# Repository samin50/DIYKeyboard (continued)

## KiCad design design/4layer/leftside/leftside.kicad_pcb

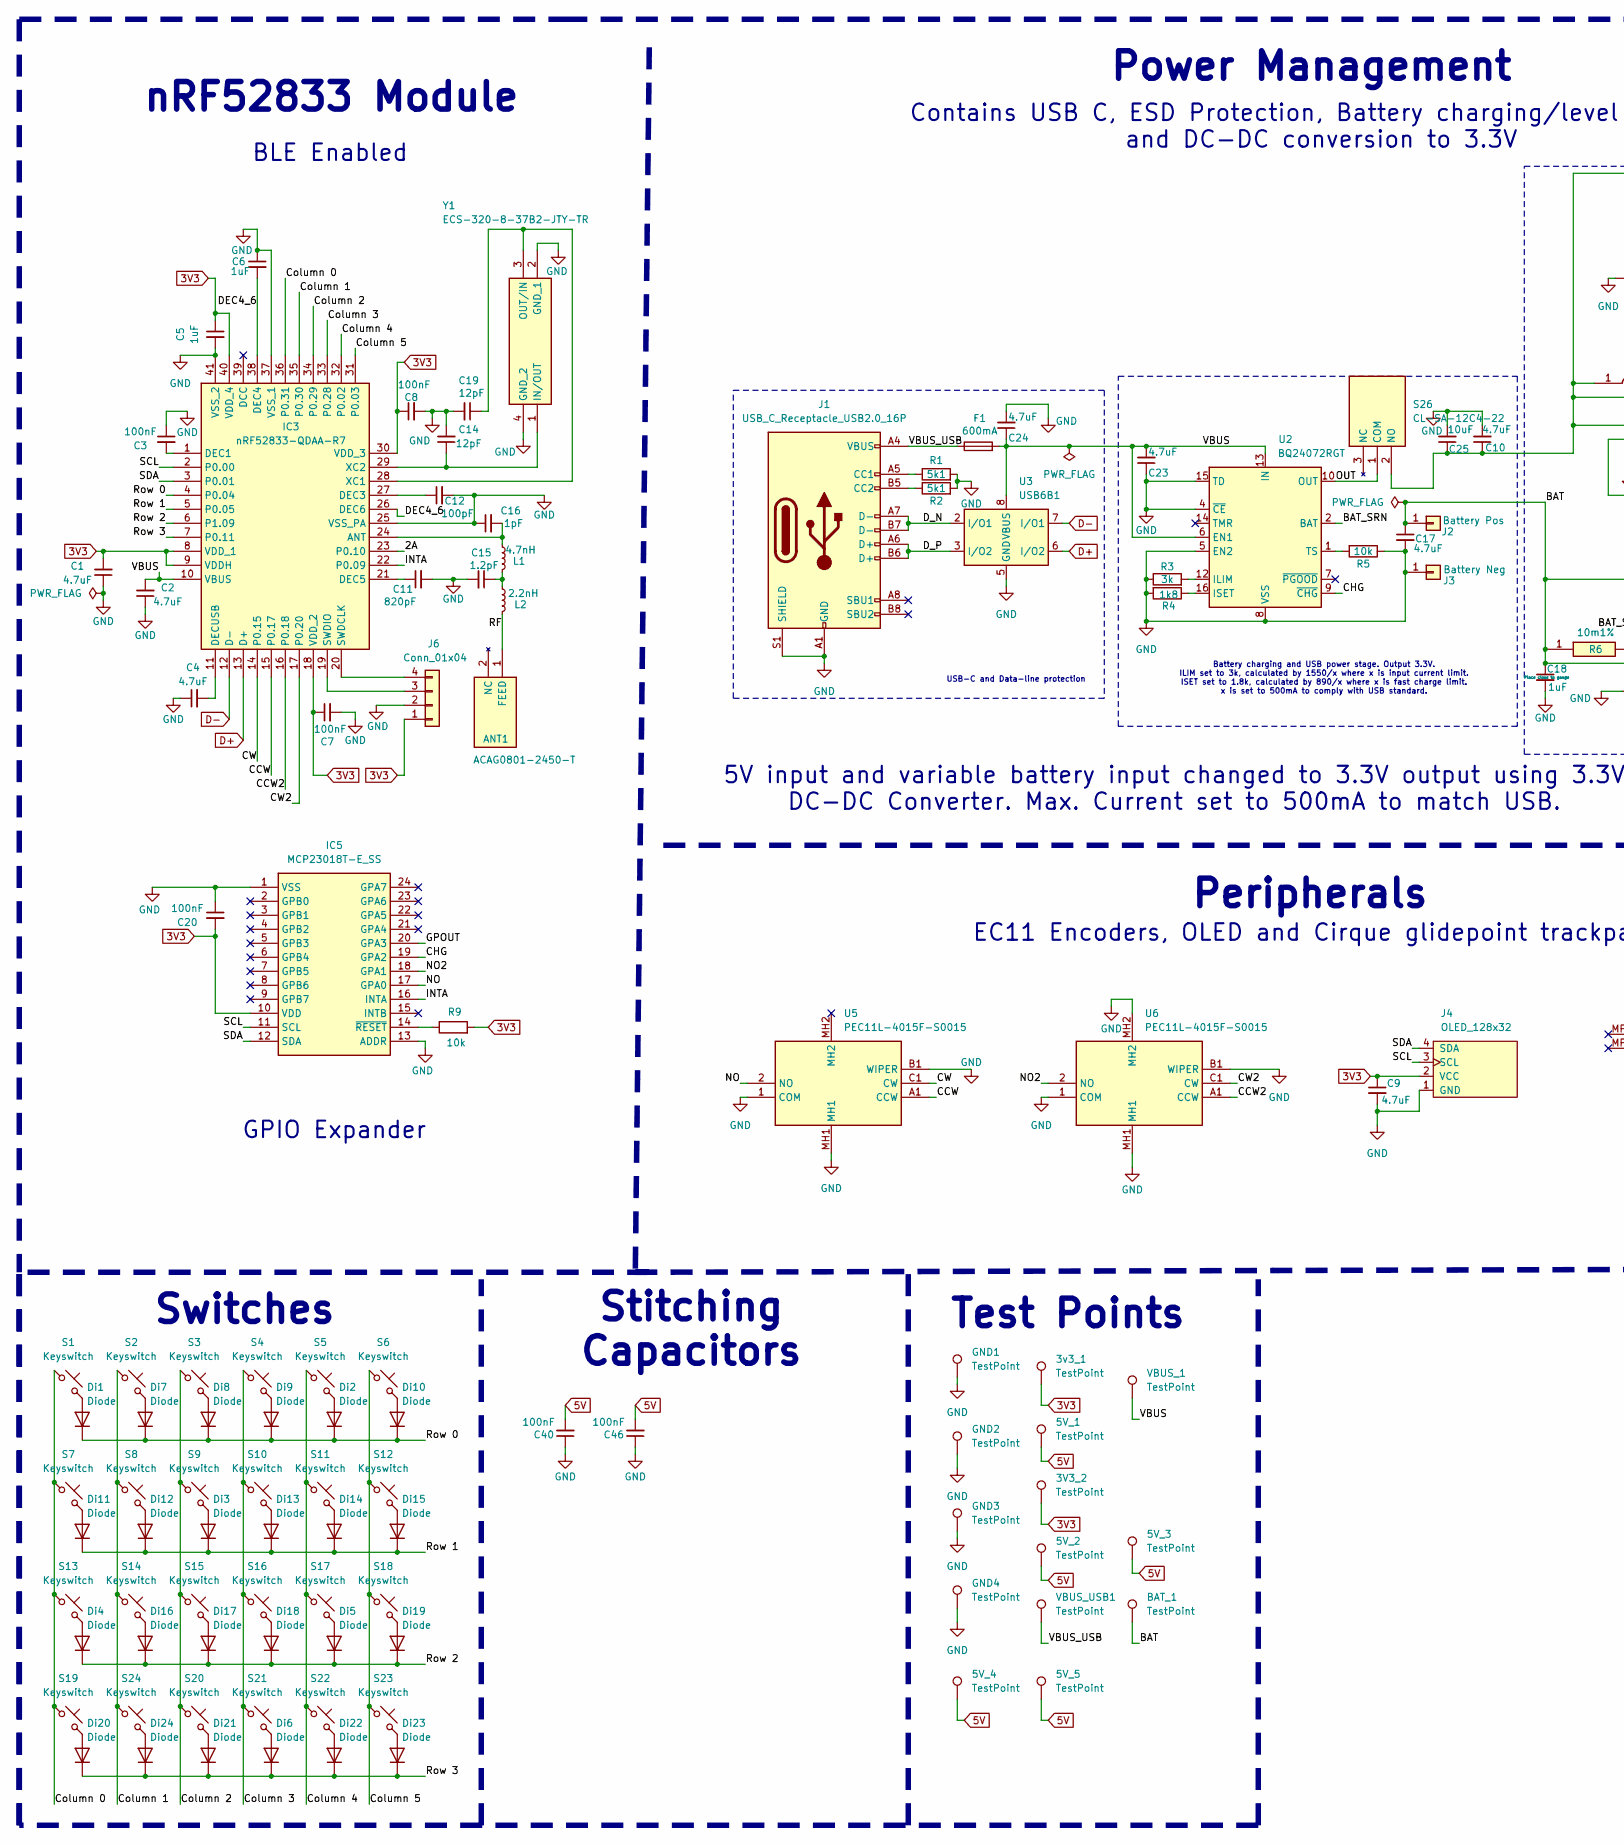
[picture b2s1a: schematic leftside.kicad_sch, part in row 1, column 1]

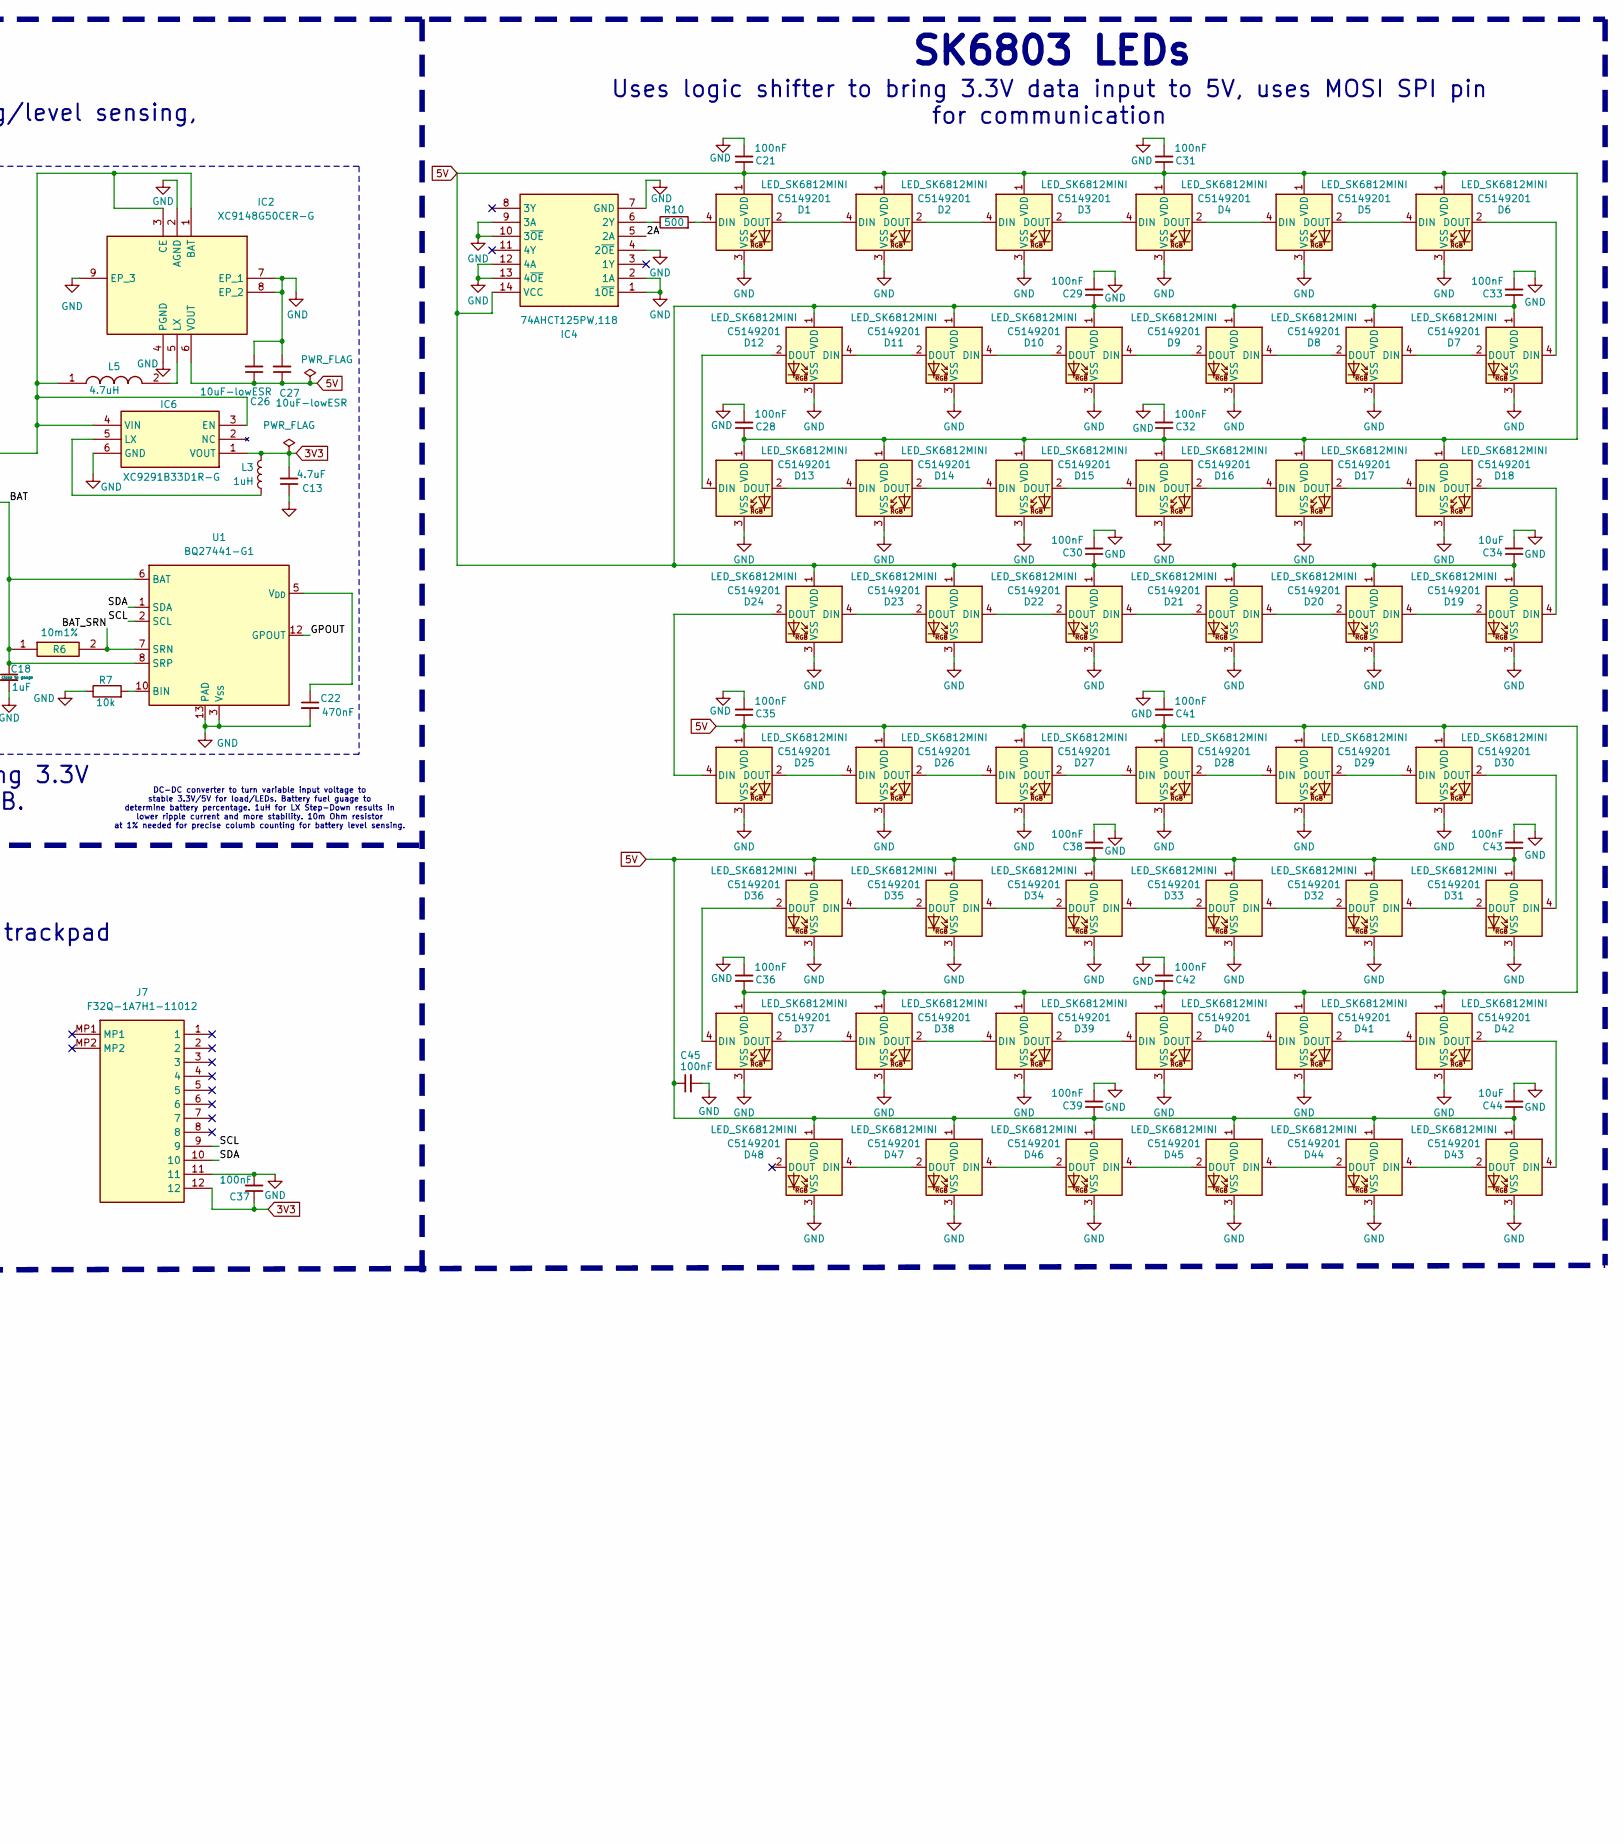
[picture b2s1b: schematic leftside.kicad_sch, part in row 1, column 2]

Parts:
3V3_2, 3v3_1, 5V_1, 5V_2, 5V_3, 5V_4, 5V_5: TestPoint; TestPoint_Pad_D1.5mm
ANT1: ACAG0801-2450-T; ANTC8010X110N; Mouser Part Number 815-G0801-2450-T
BAT_1: TestPoint; TestPoint_Pad_D1.5mm
C1, C2, C4, C9, C10, C13, C17, C23, C24: 4.7uF; Capacitor_0603
C3, C7, C8, C20, C21, C28, C29, C30, C31, C32, C33, C35, C36, C37, C38, C39, C40, C41, C42, C43, C45, C46: 100nF; Capacitor_0603
C5, C6, C18: 1uF; Capacitor_0603
C11: 820pF; Capacitor_0603
C12: 100pF; Capacitor_0603
C14, C19: 12pF; Capacitor_0603
C15: 1.2pF; Capacitor_0603
C16: 1pF; Capacitor_0603
C22: 470nF; Capacitor_0603
C25, C34, C44: 10uF; Capacitor_0603
C26, C27: 10uF-lowESR; Capacitor_0603
D1, D2, D3, D4, D5, D6, D7, D8, D9, D10, D11, D12, D13, D14, D15, D16, D17, D18, D19, D20, D21, D22, D23, D24, D25, D26, D27, D28, D29, D30, D31, D32, D33, D34, D35, D36, D37, D38, D39, D40, D41, D42, D43, D44, D45, D46, D47, D48: LED_SK6812MINI; LCSC C5149201
Di1, Di2, Di3, Di4, Di5, Di6, Di7, Di8, Di9, Di10, Di11, Di12, Di13, Di14, Di15, Di16, Di17, Di18, Di19, Di20, Di21, Di22, Di23, Di24: Diode; Diode_SOD-123
F1: 600mA; 0603L050SLYR
GND1, GND2, GND3, GND4: TestPoint; TestPoint_Pad_D1.5mm
IC2: XC9148G50CER-G; XC9147_8_USP-6C; Mouser Part Number 865-XC9148G50CER-G
IC3: nRF52833-QDAA-R7; QFN40P500X500X90-41N-D; Mouser Part Number 949-NRF52833-QDAA-R7
IC4: 74AHCT125PW,118; SOP65P640X110-14N; Mouser Part Number 771-AHCT125PW118
IC5: MCP23018T-E_SS; SOP65P780X200-24N; Mouser Part Number 579-MCP23018T-E/SS
IC6: XC9291B33D1R-G; XC9290A07E1RG; Manufacturer_Part_Number XC9291B33D1R-G
J1: USB_C_Receptacle_USB2.0_16P; USB_C_Receptacle_HRO_TYPE-C-31-M-12
J2: Battery Pos; SolderWire-2.5sqmm_1x01_D2.4mm_OD3.6mm
J3: Battery Neg; SolderWire-2.5sqmm_1x01_D2.4mm_OD3.6mm
J4: OLED_128x32
J6: Conn_01x04; PinHeader_1x04_P2.54mm_Vertical
J7: F32Q-1A7H1-11012; F32Q1A7H111012; Mouser Part Number 649-F32Q-1A7H1-11012
L1: 4.7nH; L_0603_1608Metric
L2: 2.2nH; L_0603_1608Metric
L3: 1uH; L_0603_1608Metric
L5: 4.7uH; INDC1608X80N; Mouser Part Number 963-MCHK1608T1R0MKN
R1, R2: 5k1; R_0603_1608Metric
R3: 3k; R_0603_1608Metric
R4: 1k8; R_0603_1608Metric
R5, R7, R9: 10k; R_0603_1608Metric
R6: 10m1%; RESC2012X41N; Mouser Part Number 660-TLR2ATTD10L0F
R10: 500; R_0603_1608Metric
S1, S2, S3, S4, S5, S6, S7, S8, S9, S10, S11, S12, S13, S14, S15, S16, S17, S18, S19, S20, S21, S22, S23, S24: Keyswitch; Hotswap_Choc_V1V2_Plated_1.00u
S26: CL-SA-12C4-22; CLSA12C422; Mouser Part Number 229-CL-SA-12C4-22
U1: BQ27441-G1; Texas_S-PDSO-N12
U2: BQ24072RGT; VQFN-16-1EP_3x3mm_P0.5mm_EP1.6x1.6mm
U3: USB6B1; SOIC-8_3.9x4.9mm_P1.27mm
U5, U6: PEC11L-4015F-S0015; PEC11L4015FS0015; Mouser Part Number 652-PEC11L4015FS0015
VBUS_1: TestPoint; TestPoint_Pad_D1.5mm
VBUS_USB1: TestPoint; TestPoint_Pad_D1.5mm
Y1: ECS-320-8-37B2-JTY-TR; ECS320837B2JTYTR; Mouser Part Number 520-320-8-37B2-JTYTR

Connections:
3V3: 3V3_2.1, 3v3_1.1, C1.2, C5.1, C7.1, C8.1, C9.1, C13.2, C20.2, C37.1, IC3.8 (VDD_1), IC3.9 (VDDH), IC3.18 (VDD_2), IC3.30 (VDD_3), IC3.40 (VDD_4), IC5.10 (VDD), IC6.1 (VOUT), J4.2 (VCC), J6.1, J7.12, L3.1, R9.2
5V: 5V_1.1, 5V_2.1, 5V_3.1, 5V_4.1, 5V_5.1, C21.1, C26.1, C27.1, C28.1, C29.1, C30.1, C31.1, C32.1, C33.1, C34.1, C35.1, C36.1, C38.1, C39.1, C40.2, C41.1, C42.1, C43.1, C44.1, C45.1, C46.2, D1.1 (VDD), D2.1 (VDD), D3.1 (VDD), D4.1 (VDD), D5.1 (VDD), D6.1 (VDD), D7.1 (VDD), D8.1 (VDD), D9.1 (VDD), D10.1 (VDD), D11.1 (VDD), D12.1 (VDD), D13.1 (VDD), D14.1 (VDD), D15.1 (VDD), D16.1 (VDD), D17.1 (VDD), D18.1 (VDD), D19.1 (VDD), D20.1 (VDD), D21.1 (VDD), D22.1 (VDD), D23.1 (VDD), D24.1 (VDD), D25.1 (VDD), D26.1 (VDD), D27.1 (VDD), D28.1 (VDD), D29.1 (VDD), D30.1 (VDD), D31.1 (VDD), D32.1 (VDD), D33.1 (VDD), D34.1 (VDD), D35.1 (VDD), D36.1 (VDD), D37.1 (VDD), D38.1 (VDD), D39.1 (VDD), D40.1 (VDD), D41.1 (VDD), D42.1 (VDD), D43.1 (VDD), D44.1 (VDD), D45.1 (VDD), D46.1 (VDD), D47.1 (VDD), D48.1 (VDD), IC2.6 (VOUT), IC4.14 (VCC)
/2A: IC3.23 (P0.10), IC4.5 (2A)
/BAT: BAT_1.1, C17.1, C18.1, J2.1, R6.1, U1.6 (BAT), U1.8 (SRP)
/BAT_SRN: R6.2, U1.7 (SRN), U2.2 (BAT), U2.3 (BAT)
/CCW: IC3.15 (P0.17), U5.A1 (CCW)
/CCW2: IC3.16 (P0.18), U6.A1 (CCW)
/CHG: IC5.19 (GPA2), U2.9 (~CHG)
/CW: IC3.14 (P0.15), U5.C1 (CW)
/CW2: IC3.17 (P0.20), U6.C1 (CW)
/Column 0: IC3.36 (P0.31), S1.1, S7.1, S13.1, S19.1
/Column 1: IC3.35 (P0.30), S2.1, S8.1, S14.1, S24.1
/Column 2: IC3.34 (P0.29), S3.1, S9.1, S15.1, S20.1
/Column 3: IC3.33 (P0.28), S4.1, S10.1, S16.1, S21.1
/Column 4: IC3.32 (P0.02), S5.1, S11.1, S17.1, S22.1
/Column 5: IC3.31 (P0.03), S6.1, S12.1, S18.1, S23.1
/DEC4_6: C6.2, IC3.26 (DEC6), IC3.38 (DEC4)
/D_N: J1.A7 (D-), J1.B7 (D-), U3.2 (I/O1)
/D_P: J1.A6 (D+), J1.B6 (D+), U3.3 (I/O2)
/GPOUT: IC5.20 (GPA3), U1.12 (GPOUT)
/INTA: IC3.22 (P0.09), IC5.16 (INTA)
/NO: IC5.17 (GPA0), U5.2 (NO)
/NO2: IC5.18 (GPA1), U6.2 (NO)
/OUT: S26.1 (COM), U2.10 (OUT), U2.11 (OUT)
/RF: ANT1.1 (FEED), L2.1
/Row 0: Di1.1 (K), Di2.1 (K), Di7.1 (K), Di8.1 (K), Di9.1 (K), Di10.1 (K), IC3.4 (P0.04)
/Row 1: Di3.1 (K), Di11.1 (K), Di12.1 (K), Di13.1 (K), Di14.1 (K), Di15.1 (K), IC3.5 (P0.05)
/Row 2: Di4.1 (K), Di5.1 (K), Di16.1 (K), Di17.1 (K), Di18.1 (K), Di19.1 (K), IC3.6 (P1.09)
/Row 3: Di6.1 (K), Di20.1 (K), Di21.1 (K), Di22.1 (K), Di23.1 (K), Di24.1 (K), IC3.7 (P0.11)
/SCL: IC3.2 (P0.00), IC5.11 (SCL), J4.3 (SCL), J7.9, U1.2 (SCL)
/SDA: IC3.3 (P0.01), IC5.12 (SDA), J4.4 (SDA), J7.10, U1.1 (SDA)
/VBUS: C2.2, C23.2, C24.1, F1.2, IC3.10 (VBUS), U2.6 (EN1), U2.13 (IN), U3.1 (VBUS), U3.8 (VBUS), VBUS_1.1
/VBUS_USB: F1.1, J1.A4 (VBUS), J1.A9 (VBUS), J1.B4 (VBUS), J1.B9 (VBUS), VBUS_USB1.1
D+: IC3.13 (D+), U3.6 (I/O2)
D-: IC3.12 (D-), U3.7 (I/O1)
GND: C1.1, C2.1, C3.1, C4.1, C5.2, C6.1, C7.2, C8.2, C9.2, C10.2, C11.2, C12.2, C13.1, C14.2, C15.2, C16.1, C17.2, C18.2, C19.2, C20.1, C21.2, C22.2, C23.1, C24.2, C25.2, C26.2, C27.2, C28.2, C29.2, C30.2, C31.2, C32.2, C33.2, C34.2, C35.2, C36.2, C37.2, C38.2, C39.2, C40.1, C41.2, C42.2, C43.2, C44.2, C45.2, C46.1, D1.3 (VSS), D2.3 (VSS), D3.3 (VSS), D4.3 (VSS), D5.3 (VSS), D6.3 (VSS), D7.3 (VSS), D8.3 (VSS), D9.3 (VSS), D10.3 (VSS), D11.3 (VSS), D12.3 (VSS), D13.3 (VSS), D14.3 (VSS), D15.3 (VSS), D16.3 (VSS), D17.3 (VSS), D18.3 (VSS), D19.3 (VSS), D20.3 (VSS), D21.3 (VSS), D22.3 (VSS), D23.3 (VSS), D24.3 (VSS), D25.3 (VSS), D26.3 (VSS), D27.3 (VSS), D28.3 (VSS), D29.3 (VSS), D30.3 (VSS), D31.3 (VSS), D32.3 (VSS), D33.3 (VSS), D34.3 (VSS), D35.3 (VSS), D36.3 (VSS), D37.3 (VSS), D38.3 (VSS), D39.3 (VSS), D40.3 (VSS), D41.3 (VSS), D42.3 (VSS), D43.3 (VSS), D44.3 (VSS), D45.3 (VSS), D46.3 (VSS), D47.3 (VSS), D48.3 (VSS), GND1.1, GND2.1, GND3.1, GND4.1, IC2.2 (AGND), IC2.4 (PGND), IC2.7 (EP_1), IC2.8 (EP_2), IC2.9 (EP_3), IC3.25 (VSS_PA), IC3.37 (VSS_1), IC3.41 (VSS_2), IC4.1 (1~OE), IC4.2 (1A), IC4.4 (2~OE), IC4.7 (GND), IC4.9 (3A), IC4.10 (3~OE), IC4.12 (4A), IC4.13 (4~OE), IC5.1 (VSS), IC5.13 (ADDR), IC6.6 (GND), J1.A1 (GND), J1.A12 (GND), J1.B1 (GND), J1.B12 (GND), J1.S1 (SHIELD), J3.1, J4.1 (GND), J6.2, J7.11, R1.2, R2.2, R3.1, R4.2, R5.1, R7.1, U1.3 (V_{SS}), U1.13 (PAD), U2.4 (~CE), U2.5 (EN2), U2.8 (VSS), U2.15 (TD), U2.17 (VSS), U3.4 (GND), U3.5 (GND), U5.1 (COM), U5.B1 (WIPER), U5.MH1, U6.1 (COM), U6.B1 (WIPER), U6.MH1, U6.MH2, Y1.2 (GND_1), Y1.4 (GND_2)
unnamed: C15.1, L1.2, L2.2
unnamed: D1.4 (DIN), R10.2
unnamed: D1.2 (DOUT), D2.4 (DIN)
unnamed: D2.2 (DOUT), D3.4 (DIN)
unnamed: D3.2 (DOUT), D4.4 (DIN)
unnamed: D4.2 (DOUT), D5.4 (DIN)
unnamed: D5.2 (DOUT), D6.4 (DIN)
unnamed: D6.2 (DOUT), D7.4 (DIN)
unnamed: D7.2 (DOUT), D8.4 (DIN)
unnamed: D8.2 (DOUT), D9.4 (DIN)
unnamed: D9.2 (DOUT), D10.4 (DIN)
unnamed: D10.2 (DOUT), D11.4 (DIN)
unnamed: D11.2 (DOUT), D12.4 (DIN)
unnamed: D12.2 (DOUT), D13.4 (DIN)
unnamed: D13.2 (DOUT), D14.4 (DIN)
unnamed: D14.2 (DOUT), D15.4 (DIN)
unnamed: D15.2 (DOUT), D16.4 (DIN)
unnamed: D16.2 (DOUT), D17.4 (DIN)
unnamed: D17.2 (DOUT), D18.4 (DIN)
unnamed: D18.2 (DOUT), D19.4 (DIN)
unnamed: D19.2 (DOUT), D20.4 (DIN)
unnamed: D20.2 (DOUT), D21.4 (DIN)
unnamed: D21.2 (DOUT), D22.4 (DIN)
unnamed: D22.2 (DOUT), D23.4 (DIN)
unnamed: D23.2 (DOUT), D24.4 (DIN)
unnamed: D24.2 (DOUT), D25.4 (DIN)
unnamed: D25.2 (DOUT), D26.4 (DIN)
unnamed: D26.2 (DOUT), D27.4 (DIN)
unnamed: D27.2 (DOUT), D28.4 (DIN)
unnamed: D28.2 (DOUT), D29.4 (DIN)
unnamed: D29.2 (DOUT), D30.4 (DIN)
unnamed: D30.2 (DOUT), D31.4 (DIN)
unnamed: D31.2 (DOUT), D32.4 (DIN)
unnamed: D32.2 (DOUT), D33.4 (DIN)
unnamed: D33.2 (DOUT), D34.4 (DIN)
unnamed: D34.2 (DOUT), D35.4 (DIN)
unnamed: D35.2 (DOUT), D36.4 (DIN)
unnamed: D36.2 (DOUT), D37.4 (DIN)
unnamed: D37.2 (DOUT), D38.4 (DIN)
unnamed: D38.2 (DOUT), D39.4 (DIN)
unnamed: D39.2 (DOUT), D40.4 (DIN)
unnamed: D40.2 (DOUT), D41.4 (DIN)
unnamed: D41.2 (DOUT), D42.4 (DIN)
unnamed: D42.2 (DOUT), D43.4 (DIN)
unnamed: D43.2 (DOUT), D44.4 (DIN)
unnamed: D44.2 (DOUT), D45.4 (DIN)
unnamed: D45.2 (DOUT), D46.4 (DIN)
unnamed: D46.2 (DOUT), D47.4 (DIN)
unnamed: D47.2 (DOUT), D48.4 (DIN)
unnamed: Di1.2 (A), S1.2
unnamed: Di2.2 (A), S5.2
unnamed: Di3.2 (A), S9.2
unnamed: Di4.2 (A), S13.2
unnamed: Di5.2 (A), S17.2
unnamed: Di6.2 (A), S21.2
unnamed: Di7.2 (A), S2.2
unnamed: Di8.2 (A), S3.2
unnamed: Di9.2 (A), S4.2
unnamed: Di10.2 (A), S6.2
unnamed: Di11.2 (A), S7.2
unnamed: Di12.2 (A), S8.2
unnamed: Di13.2 (A), S10.2
unnamed: Di14.2 (A), S11.2
unnamed: Di15.2 (A), S12.2
unnamed: Di16.2 (A), S14.2
unnamed: Di17.2 (A), S15.2
unnamed: Di18.2 (A), S16.2
unnamed: Di19.2 (A), S18.2
unnamed: Di20.2 (A), S19.2
unnamed: Di21.2 (A), S20.2
unnamed: Di22.2 (A), S22.2
unnamed: Di23.2 (A), S23.2
unnamed: Di24.2 (A), S24.2
unnamed: C10.1, C25.1, IC2.1 (BAT), IC2.3 (CE), IC6.3 (EN), IC6.4 (VIN), L5.1, S26.2 (NO)
unnamed: IC2.5 (LX), L5.2
unnamed: C16.2, IC3.24 (ANT), L1.1
unnamed: C3.2, IC3.1 (DEC1)
unnamed: C12.1, IC3.27 (DEC3)
unnamed: C11.1, IC3.21 (DEC5)
unnamed: C4.2, IC3.11 (DECUSB)
unnamed: IC3.20 (SWDCLK), J6.4
unnamed: IC3.19 (SWDIO), J6.3
unnamed: C19.1, IC3.28 (XC1), Y1.3 (OUT/IN)
unnamed: C14.1, IC3.29 (XC2), Y1.1 (IN/OUT)
unnamed: IC4.6 (2Y), R10.1
unnamed: IC5.14 (~RESET), R9.1
unnamed: IC6.5 (LX), L3.2
unnamed: J1.A5 (CC1), R1.1
unnamed: J1.B5 (CC2), R2.1
unnamed: R7.2, U1.10 (BIN)
unnamed: C22.1, U1.5 (V_{DD})
unnamed: R3.2, U2.12 (ILIM)
unnamed: R4.1, U2.16 (ISET)
unnamed: R5.2, U2.1 (TS)

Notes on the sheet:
Test Points
SK6803 LEDs
nRF52833 Module
GPIO Expander
BLE Enabled
DC-DC converter to turn variable input voltage to stable 3.3V/5V for load/LEDs. Battery fuel guage to determine battery percentage. 1uH for LX Step-Down results in lower ripple current and more stability. 10m Ohm resistor at 1% needed for precise columb counting for battery level sensing.
Power Management
Battery charging and USB power stage. Output 3.3V. ILIM set to 3k, calculated by 1550/x where x is input current limit. ISET set to 1.8k, calculated by 890/x where x is fast charge limit. x is set to 500mA to comply with USB standard.
USB-C and Data-line protection
Peripherals
Switches
EC11 Encoders, OLED and Cirque glidepoint trackpad
5V input and variable battery input changed to 3.3V output using 3.3V DC-DC Converter. Max. Current set to 500mA to match USB.
Contains USB C, ESD Protection, Battery charging/level sensing, and DC-DC conversion to 3.3V
Uses logic shifter to bring 3.3V data input to 5V, uses MOSI SPI pin for communication
Stitching Capacitors

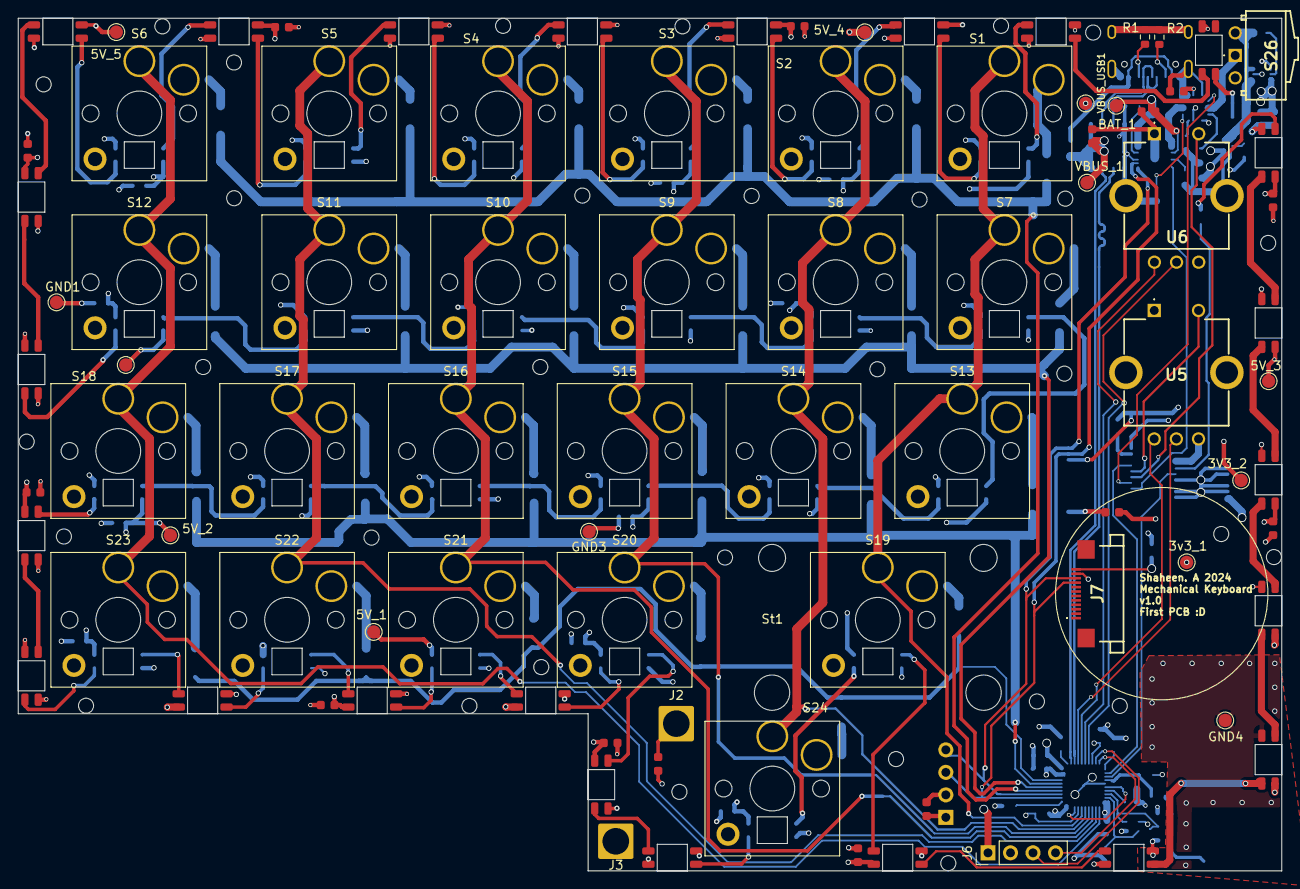
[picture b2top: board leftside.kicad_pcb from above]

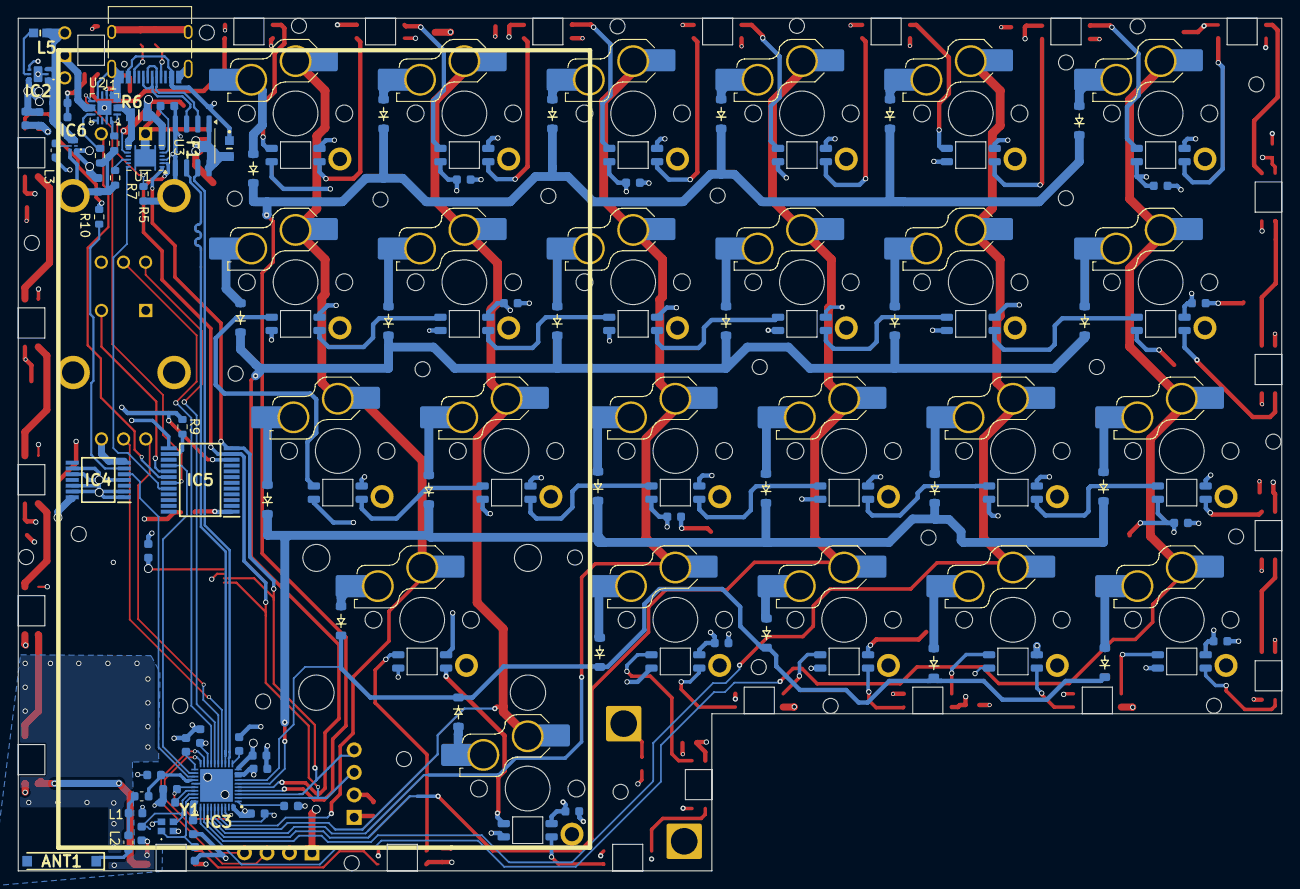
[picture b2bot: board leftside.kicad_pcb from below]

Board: 4 copper layers, 142.6 x 96.2 mm, 190 parts (102 on the bottom side), 130 nets.

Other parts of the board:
St1: Stabilizer_MX_2.00u

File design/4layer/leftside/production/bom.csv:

Designator,Footprint,Quantity,Value,LCSC Part #
"3V3_2, 3v3_1, 5V_1, 5V_2, 5V_3, 5V_4, 5V_5, BAT_1, GND1, GND2, GND3, GND4, VBUS_1, VBUS_USB1",TestPoint_Pad_D1.5mm,14,TestPoint,
ANT1,ANTC8010X110N,1,ACAG0801-2450-T,
"C1, C10, C13, C17, C2, C23, C24, C4, C9",Capacitor_0603,9,4.7uF,
C11,Capacitor_0603,1,820pF,
C12,Capacitor_0603,1,100pF,
"C14, C19",Capacitor_0603,2,12pF,
C15,Capacitor_0603,1,1.2pF,
C16,Capacitor_0603,1,1pF,
"C18, C5, C6",Capacitor_0603,3,1uF,
"C20, C21, C28, C29, C3, C30, C31, C32, C33, C35, C36, C37, C38, C39, C40, C41, C42, C43, C45, C46, C7, C8",Capacitor_0603,22,100nF,
C22,Capacitor_0603,1,470nF,
"C25, C34, C44",Capacitor_0603,3,10uF,
"C26, C27",Capacitor_0603,2,10uF-lowESR,
"D1, D10, D11, D12, D13, D14, D15, D16, D17, D18, D19, D2, D20, D21, D22, D23, D24, D25, D26, D27, D28, D29, D3, D30, D31, D32, D33, D34, D35, D36, D37, D38, D39, D4, D40, D41, D42, D43, D44, D45, D46, D47, D48, D5, D6, D7, D8, D9",LED_SK6812MINI,48,LED_SK6812MINI,C5149201
"Di1, Di10, Di11, Di12, Di13, Di14, Di15, Di16, Di17, Di18, Di19, Di2, Di20, Di21, Di22, Di23, Di24, Di3, Di4, Di5, Di6, Di7, Di8, Di9",Diode_SOD-123,24,Diode,
F1,0603L050SLYR,1,600mA,
IC2,XC9147_8_USP-6C,1,XC9148G50CER-G,
IC3,QFN40P500X500X90-41N-D,1,nRF52833-QDAA-R7,
IC4,SOP65P640X110-14N,1,"74AHCT125PW,118",
IC5,SOP65P780X200-24N,1,MCP23018T-E_SS,
IC6,XC9290A07E1RG,1,XC9291B33D1R-G,
J1,USB_C_Receptacle_HRO_TYPE-C-31-M-12,1,USB_C_Receptacle_USB2.0_16P,
J2,SolderWire-2.5sqmm_1x01_D2.4mm_OD3.6mm,1,Battery Pos,
J3,SolderWire-2.5sqmm_1x01_D2.4mm_OD3.6mm,1,Battery Neg,
J4,OLED_128x32,1,OLED_128x32,
J6,PinHeader_1x04_P2.54mm_Vertical,1,Conn_01x04,
J7,F32Q1A7H111012,1,F32Q-1A7H1-11012,
L1,0603,1,4.7nH,
L2,0603,1,2.2nH,
L3,0603,1,1uH,
L5,INDC1608X80N,1,MCHK1608T1R0MKN,
"R1, R2",0603,2,5k1,
R10,0603,1,500,
R3,0603,1,3k,
R4,0603,1,1k8,
"R5, R7, R9",0603,3,10k,
R6,RESC2012X41N,1,10m1%,
"S1, S10, S11, S12, S13, S14, S15, S16, S17, S18, S19, S2, S20, S21, S22, S23, S24, S3, S4, S5, S6, S7, S8, S9",Hotswap_Choc_V1V2_Plated_1.00u,24,Keyswitch,
S26,CLSA12C422,1,CL-SA-12C4-22,
U1,Texas_S-PDSO-N12,1,BQ27441-G1,
U2,VQFN-16-1EP_3x3mm_P0.5mm_EP1.6x1.6mm,1,BQ24072RGT,
U3,SOIC-8_3.9x4.9mm_P1.27mm,1,USB6B1,
"U5, U6",PEC11L4015FS0015,2,PEC11L-4015F-S0015,
Y1,ECS320837B2JTYTR,1,ECS-320-8-37B2-JTY-TR,

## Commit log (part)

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2024-09-27 initial designs
2024-09-28 add coloured layout
2024-09-30 setup kicad
2024-10-01 remove library from repo
2024-10-04 add power management
2024-10-05 complete power management
2024-10-05 begin adding peripherals
2024-10-05 add peripherals
2024-10-05 add step up converter for LEDs
2024-10-05 add LEDs
2024-10-05 complete schematic
2024-10-07 pcb place switches, leds, diodes and stabiliser right side
2024-10-10 add power planes
2024-10-12 vbus routing
2024-10-21 prepare to change switch footprint
2024-10-21 prepare to reroute for antenna
2024-11-16 begin to relocate usb c data lines
2024-11-18 prepare to move around traces for better routing
2024-11-18 finish switch routing
2024-11-21 no errors drc
2024-11-22 routed no errors
2024-11-30 uart switch
2024-11-30 swd pins and mounting holes
2024-11-30 prepare RS production
2024-11-30 begin to remove unnecessary vias
2024-11-30 production save prepare for left side
2024-12-01 prepare for left side and reorganise
2024-12-01 successfully create pcb layout mirror script
2024-12-02 correct fuel gauge and crystal
2024-12-03 prepare to reroute
2024-12-07 prepare to make test board
2024-12-19 complete right side reroute
2024-12-19 remove old right side routing
2024-12-22 place edge lights
2024-12-22 reroute power input
2024-12-22 begin making space for led near switch
2024-12-26 rerouting 3v3 transformer
2024-12-26 begin to move gpio expander
2024-12-26 begin to reroute leds
2024-12-27 prepare to add cut out for battery
2024-12-28 prepare to correct bq27441
2024-12-29 right side backlight complete
2024-12-29 scaling and positioning
2024-12-30 restructure for right side and add correct mounting holes
2025-01-01 prepare to combine left and right into one pcb
2025-01-03 verify connections, make erc happy
2025-01-04 begin routing leftside
2025-01-05 begin to move power plane
2025-01-06 LS: prepare to flip 5V dcdc
2025-01-06 LS routing complete
2025-01-06 LS RS no error
2025-01-07 expand power planes
2025-01-07 RS LS Complete
2025-01-08 create first merged gerber, prepare to fix board outline
2025-01-10 submit merged design and do proper outline for boards
2025-01-26 pcb arrive, prepare for testing board
2025-02-17 setup nrf connect
2025-02-23 rearrange to begin designing 2 layer board
2025-02-25 prepare to wire
2025-03-03 5v led power plane added
2025-03-19 RS two layer complete
2025-03-20 LS two layer complete
2025-03-22 place components for RS 2 layer
2025-03-27 prepare to add in EVQWGD001
2025-11-16 New layout
2025-11-24 RS begin to replace USB lines to shift 5V planes
2026-01-23 begin better, more systematic 2 layer wiring
2026-02-08 V3 prep
2026-02-16 Left side pre-stich
2026-04-13 LS Kicad 10 migration
2026-04-13 cleanup
2026-06-06 RS LED wiring
2026-06-06 Add testpoints and correct violations
2026-06-06 Fill all missing connections, except zone stitching vias
2026-06-17 Commit before changing via sizes
2026-06-17 convert all RS minimum vias to reduce cost
2026-06-17 Convert all LS vias
2026-06-20 Add drill holes and via fencing/stitching, PCB DONE
2026-06-21 Preparation for panelisation
2026-06-21 Create auto mousebite adder
